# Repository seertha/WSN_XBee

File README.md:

# WSN_XBee
Red de sensores inalámbricos utilizando módulos de comunicación XBee.

Proyecto en desarrollo.

Pruebas en RPi2.

Se utiliza la placa adaptadora para GPIO v1_3

Se utiliza un menú inicial de control para seleccionar el programa principal

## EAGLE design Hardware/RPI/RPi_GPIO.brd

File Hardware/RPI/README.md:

Archivos Eagle para la placa adaptadora GPIO

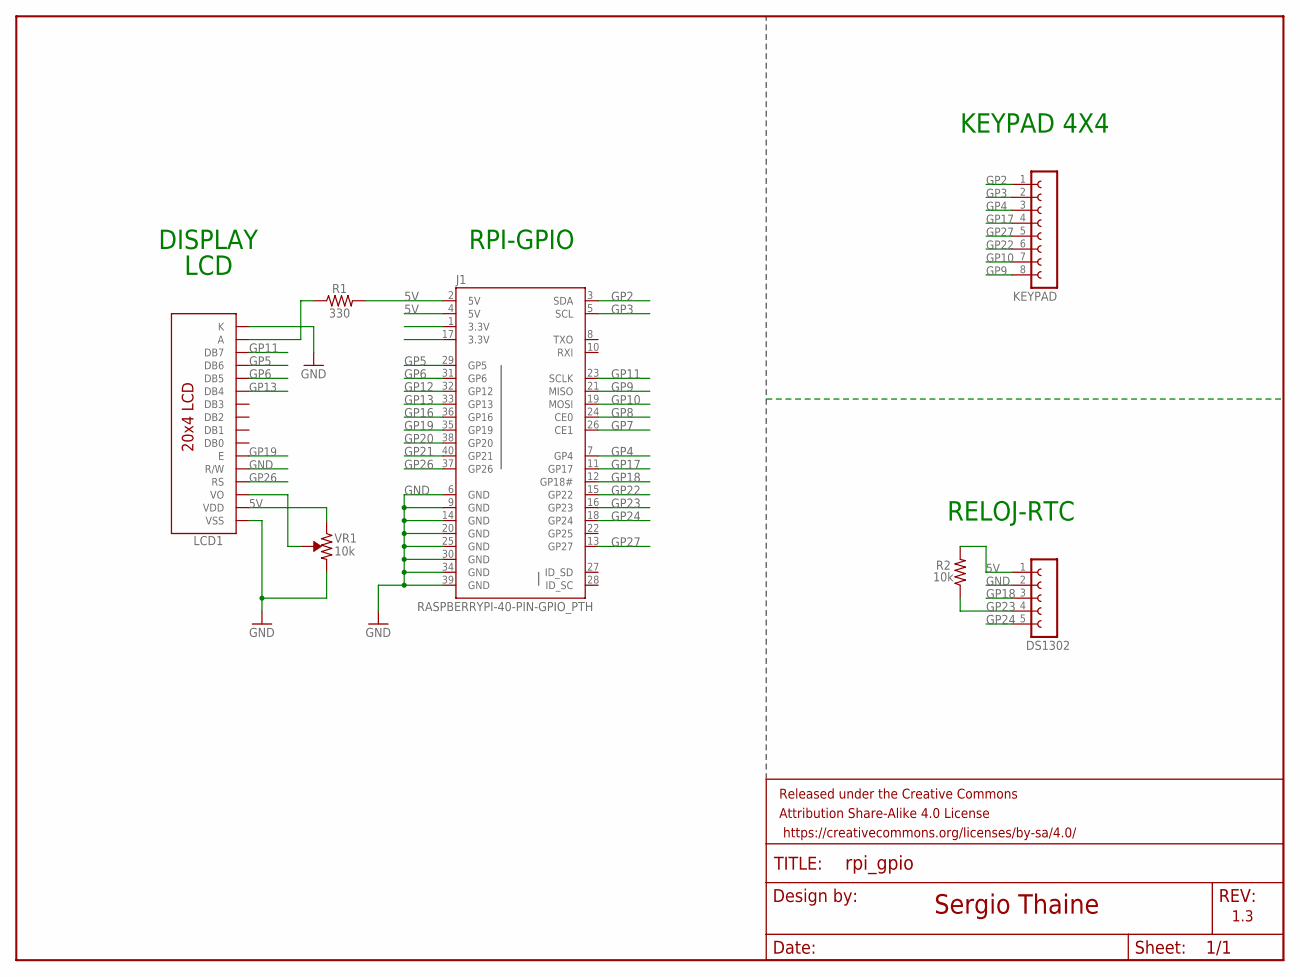
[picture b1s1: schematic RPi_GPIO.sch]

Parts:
DS1302: FE05-1
FRAME1: FRAME-LETTERNO_PACKAGE; DUMMY
J1: RASPBERRYPI-40-PIN-GPIO_PTH; 2X20_SHROUDED
KEYPAD: FE08-1; FE08
LCD1: LCD-16X2NOHOLES; LCD-16X2_NOHOLESNOSILK
R1: 330; AXIAL-0.3
R2: 10k; AXIAL-0.3
VR1: 10k; TRIMPOT-PTH-3386U

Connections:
5V: DS1302.1, J1.2 (5V), J1.4 (5V), LCD1.2 (VDD), R1.P$2 (2), R2.P$2 (2), VR1.3 (CW)
GND: DS1302.2, J1.6 (GND), J1.9 (GND), J1.14 (GND), J1.20 (GND), J1.25 (GND), J1.30 (GND), J1.34 (GND), J1.39 (GND), LCD1.1 (VSS), LCD1.5 (R/W), LCD1.16 (K), VR1.1 (CCW)
GP2: J1.3 (SDA), KEYPAD.1
GP3: J1.5 (SCL), KEYPAD.2
GP4: J1.7 (GP4), KEYPAD.3
GP5: J1.29 (GP5), LCD1.13 (DB6)
GP6: J1.31 (GP6), LCD1.12 (DB5)
GP7: J1.26 (CE1)
GP8: J1.24 (CE0)
GP9: J1.21 (MISO), KEYPAD.8
GP10: J1.19 (MOSI), KEYPAD.7
GP11: J1.23 (SCLK), LCD1.14 (DB7)
GP12: J1.32 (GP12)
GP13: J1.33 (GP13), LCD1.11 (DB4)
GP16: J1.36 (GP16)
GP17: J1.11 (GP17), KEYPAD.4
GP18: DS1302.3, J1.12 (GP18#)
GP19: J1.35 (GP19), LCD1.6 (E)
GP20: J1.38 (GP20)
GP21: J1.40 (GP21)
GP22: J1.15 (GP22), KEYPAD.6
GP23: DS1302.4, J1.16 (GP23), R2.P$1 (1)
GP24: DS1302.5, J1.18 (GP24)
GP26: J1.37 (GP26), LCD1.4 (RS)
GP27: J1.13 (GP27), KEYPAD.5
unnamed: LCD1.3 (VO), VR1.2 (WIPER)
unnamed: LCD1.15 (A), R1.P$1 (1)

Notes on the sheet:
1.3
Sergio Thaine
KEYPAD 4X4
RELOJ-RTC
RPI-GPIO
LCD
DISPLAY

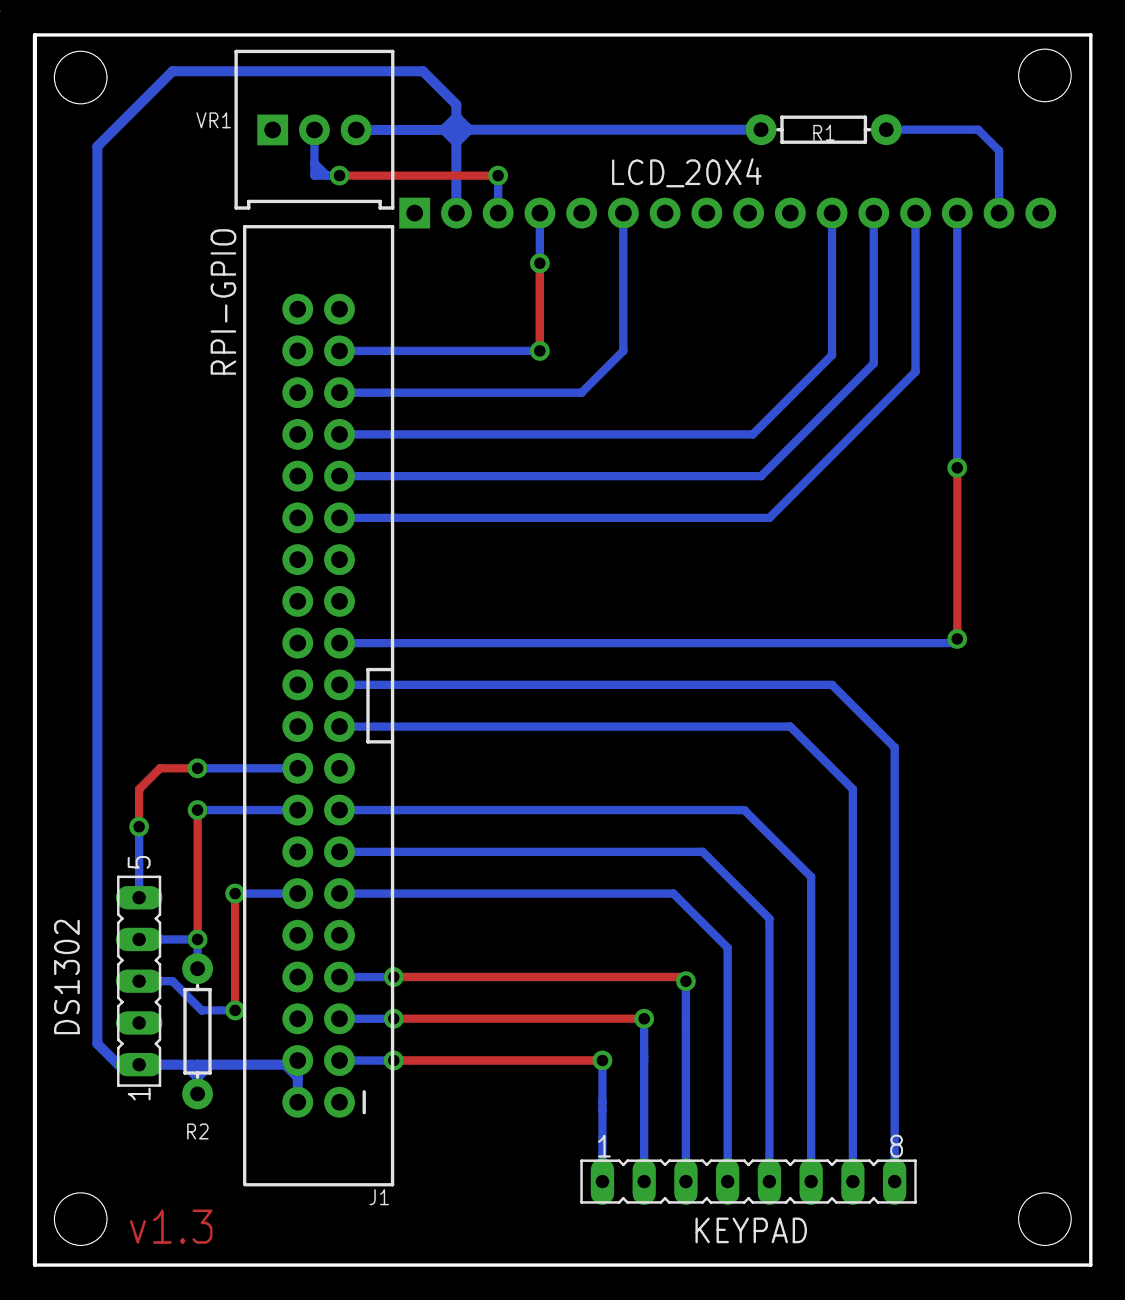
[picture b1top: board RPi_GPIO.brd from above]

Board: 2 copper layers, 64.2 x 74.9 mm, 8 parts (0 on the bottom side), 21 nets.

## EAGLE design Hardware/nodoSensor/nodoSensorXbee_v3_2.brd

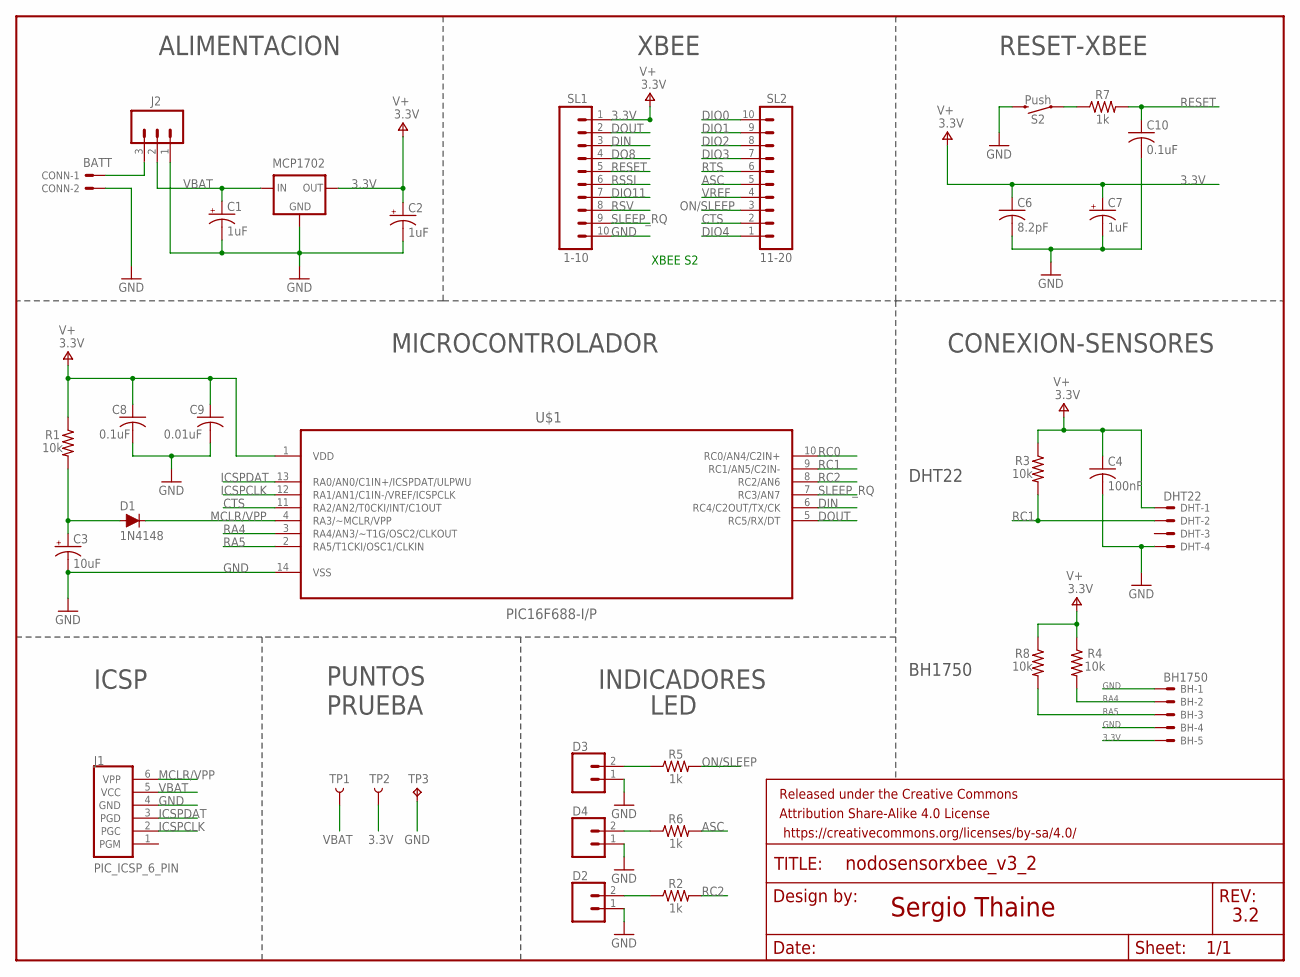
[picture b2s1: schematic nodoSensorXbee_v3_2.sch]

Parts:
BH: BH1750; 6410-05
C1, C2, C7: 1uF; E2-5
C3: 10uF; E2-5
C4: 100nF; C025-030X050
C6: 8.2pF; C025-030X050
C8, C10: 0.1uF; C025-030X050
C9: 0.01uF; C025-030X050
CONN: BATT; 6410-02
D1: 1N4148; DIODE-1N4148
D2, D3, D4: CONN_02POLAR; MOLEX-1X2
DHT: DHT22; 6410-04
FRAME1: FRAME-LETTERNO_PACKAGE; DUMMY
J1: PIC_ICSP_6_PIN; MOLEX-1X6
J2: CONN_03POLAR; MOLEX-1X3
MCP1702: 3.3v; TO92
R1, R3, R4, R8: 10k; AXIAL-0.3-KIT
R2, R5, R6, R7: 1k; AXIAL-0.3-KIT
S2: Push; TACTILE_SWITCH_PTH_6.0MM
SL1: 1-10; 10P
SL2: 11-20; 10P
TP1: VBAT; PAD.03X.05
TP2: 3.3V; PAD.03X.05
TP3: TPPAD1-13; P1-13
U$1: PIC16F688-I/P; DIP254P762X533-14

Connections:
3.3V: BH.5, C2.+, C4.1, C6.1, C7.+, C8.1, C9.1, DHT.1, MCP1702.3 (OUT), R1.P$1 (1), R3.P$1 (1), R4.P$1 (1), R8.P$1 (1), SL1.1, TP2.P$1, U$1.1 (VDD)
ASC: R6.P$2 (2), SL2.5
CTS: SL2.2, U$1.11 (RA2/AN2/T0CKI/INT/C1OUT)
DIN: SL1.3, U$1.6 (RC4/C2OUT/TX/CK)
DIO0: SL2.10
DIO1: SL2.9
DIO2: SL2.8
DIO3: SL2.7
DIO4: SL2.1
DIO11: SL1.7
DO8: SL1.4
DOUT: SL1.2, U$1.5 (RC5/RX/DT)
GND: BH.1, BH.4, C1.-, C2.-, C3.-, C4.2, C6.2, C7.-, C8.2, C9.2, C10.2, CONN.2, D2.1, D3.1, D4.1, DHT.4, J1.4 (GND), J2.1, MCP1702.1 (GND), S2.3 (2), SL1.10, TP3.TP, U$1.14 (VSS)
ICSPCLK: J1.2 (PGC), U$1.12 (RA1/AN1/C1IN-/VREF/ICSPCLK)
ICSPDAT: J1.3 (PGD), U$1.13 (RA0/AN0/C1IN+/ICSPDAT/ULPWU)
MCLR/VPP: D1.C, J1.6 (VPP), U$1.4 (RA3/~MCLR/VPP)
unnamed: CONN.1, J2.3
unnamed: C3.+, D1.A, R1.P$2 (2)
unnamed: D3.2, R5.P$1 (1)
unnamed: D4.2, R6.P$1 (1)
unnamed: D2.2, R2.P$1 (1)
unnamed: R7.P$1 (1), S2.1
ON/SLEEP: R5.P$2 (2), SL2.3
RA4: BH.2, R4.P$2 (2), U$1.3 (RA4/AN3/~T1G/OSC2/CLKOUT)
RA5: BH.3, R8.P$2 (2), U$1.2 (RA5/T1CKI/OSC1/CLKIN)
RC0: U$1.10 (RC0/AN4/C2IN+)
RC1: DHT.2, R3.P$2 (2), U$1.9 (RC1/AN5/C2IN-)
RC2: R2.P$2 (2), U$1.8 (RC2/AN6)
RESET: C10.1, R7.P$2 (2), SL1.5
RSSI: SL1.6
RSV: SL1.8
RTS: SL2.6
SLEEP_RQ: SL1.9, U$1.7 (RC3/AN7)
VBAT: C1.+, J1.5 (VCC), J2.2, MCP1702.2 (IN), TP1.P$1
VREF: SL2.4

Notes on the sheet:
XBEE S2
Sergio Thaine
3.2
3.3V
ALIMENTACION
XBEE
RESET-XBEE
CONEXION-SENSORES
MICROCONTROLADOR
DHT22
BH1750
ICSP
PUNTOS PRUEBA
LED
INDICADORES

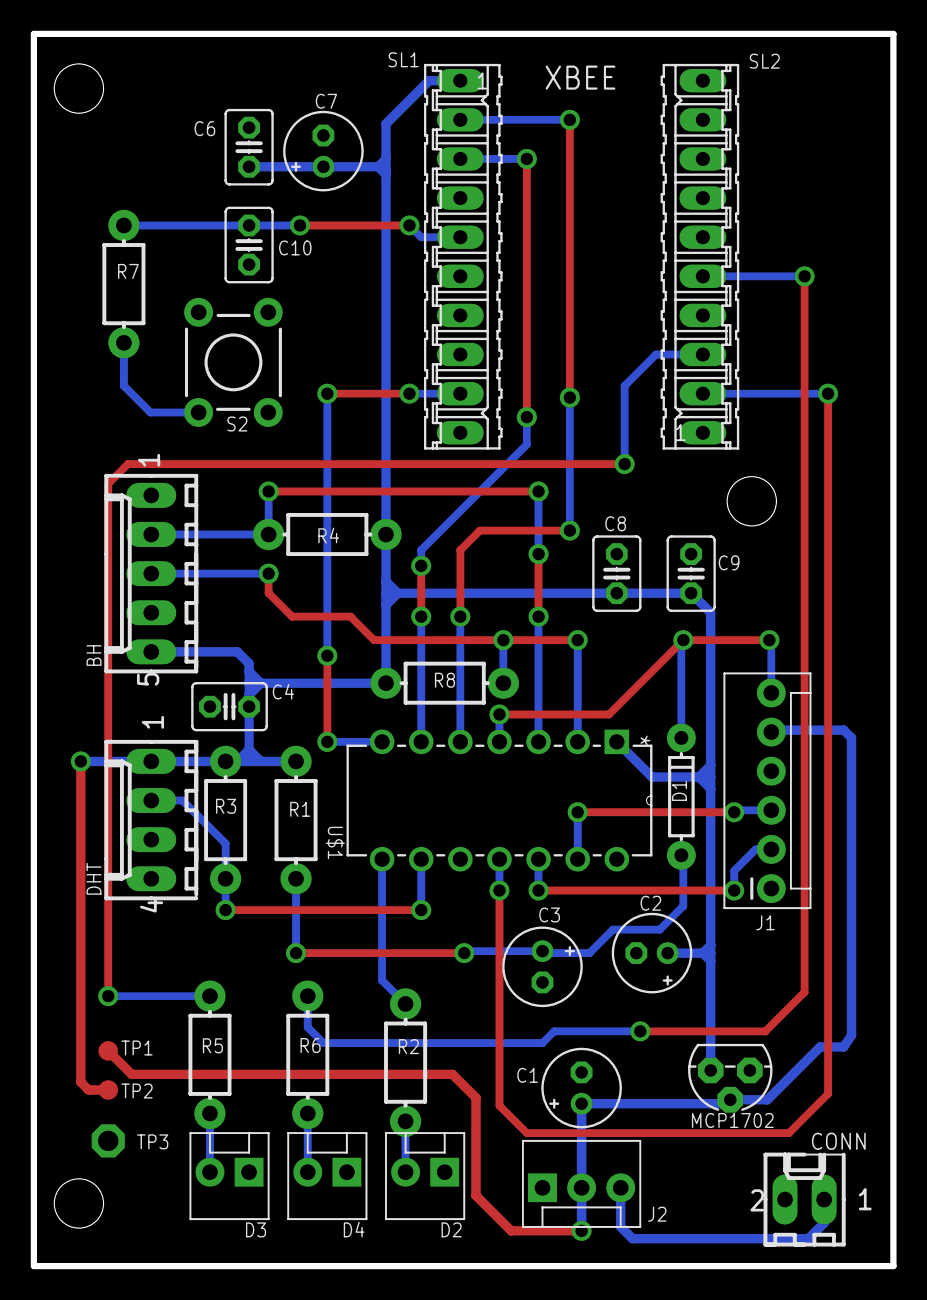
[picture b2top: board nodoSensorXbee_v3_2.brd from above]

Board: 2 copper layers, 55.8 x 80.0 mm, 35 parts (0 on the bottom side), 23 nets.

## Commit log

2017-06-18 Inicio de repositorio
2017-06-18 correciones menores
2017-06-19 xbee nodo creado y probado
2017-06-20 IndexError y Unicode Error
2017-06-21 correccion errores
2017-07-09 serial port close
2017-07-10 inicio basedatos
2017-07-14 prueba de funcionamiento general
2017-07-18 prueba base automatica
2017-07-18 borrado de comentarios
2017-07-18 Update README.md
    Inicio del repositorio
2017-07-18 Update modulosXbee.py
    Corrección en la dirección de la base de datos
2017-07-19 cambios readme
2017-07-19 cambios direccion db
2017-07-19 Update README.md
    actualizacion Readme
2017-07-19 Update README.md
    cambios readme
2017-07-19 prueba vscode
2017-07-19 prueba lcd
2017-07-19 Delete lcd_test01
    archivos innecesarios
2017-07-19 corrección lcd init
2017-07-20 cambios para pruebas con LCD
2017-08-07 cambios en lcd_db_test
2017-08-08 progrma de prueba para menu con pulsador
2017-08-08 correción de errores
2017-08-09 solucion de problemas
2017-08-09 en funcionamiento basico
2017-08-09 menu nodos sensor prueba
2017-08-10 bases de datos para pruebas
2017-08-11 configuracion de datos para pruebas
2017-08-12 correccion de errores
2017-08-12 añadiendo datos
2017-09-20 modificaciones en la visualizacion
2017-09-21 modificación para lcd 20x4
2017-09-22 corrección de errores
2017-09-22 módulo para el manejo de la base de datos incluido
2017-09-22 módulo para el manejo de la base de datos
2017-10-16 archivos para la visualizacion en el displat lcd
2018-01-05 Update README.md
    Nueva rama creada para realizar pruebas con la placa adaptadora para GPIO v1_3
2018-03-20 Corrección en los pines de control para el teclado y la pantalla lcd
2018-03-20 Inclusión de módulo db
2018-03-20 py cache display y teclado
2018-03-21 corrección formato fecha_hora
2018-03-27 cambio en el orden de ficheros
2018-03-28 Menu inicial agragado (parcial)
2018-03-28 Update README.md
    Se añade el menú de control inicial
2018-03-28 Ampliación de menu inicio
2018-03-29 Registro de teclado
2018-03-29 Prueba de inicio
2018-03-29 archivo pendiente
2018-03-29 sin cambios
2018-03-29 versiones de prueba
2018-03-29 pruebas con módulo pantallaLCD
2018-03-31 información de red añadida a la pantalla infoGen
2018-04-02 pantalla opciones añadida a selección de modo
2018-04-02 métodos reiniciar/apagar incluidos
2018-04-03 correcciones en pantalla opciones
2018-04-04 corrección info general nodos en red
2018-04-04 pycache update
2018-04-05 pantalla RESUMEN-PROMEDIO corregida
2018-04-05 maxMin día corregido
2018-04-16 Update README.md
    Branch logging
2018-04-16 eliminación de archivos innecesarios o duplicados
2018-04-17 pruebas con registros logs
2018-04-17 carpeta logs creada
2018-04-17 Corrección de errores y pruebas de logs
2018-04-18 Código alternativo en comentarios quitado
2018-04-21 registro de logs al conectarse los nodos sensores
2020-02-07 Set theme jekyll-theme-minimal
2020-02-07 gitignore añadido
2020-02-07 vscode gitignore
2020-02-07 archivo borrado
2020-02-07 .vscode borrado
2020-02-07 Create index.html
    página index.html
2020-02-07 prueba index
2020-02-18 Archivos para github pages
2020-02-18 Create README.md
    Carpeta Hardware creada
2020-02-18 Create README.md
    Carpeta Software creada
2020-02-18 Create README.md
    Carpeta PIC16F688 creada
2020-02-18 Create README.md
    Carpeta RPI creada
2020-02-18 Create README.md
    Carpeta XBEE creada
2020-02-18 Update README.md
    Xbee añadido
2020-02-18 Rename visualizacion_lcd2.py to Software/RPI/visualizacion_lcd2.py
    Cambio de ubicación a Software/RPI/
2020-02-18 Rename teclado_4x4.py to Software/RPI/teclado_4x4.py
    Cambio de ubicación a Software/RPI/
2020-02-18 Rename principal.py to Software/RPI/principal.py
    Cambio de ubicación a Software/RPI/
2020-02-18 Rename pantallas2.py to Software/RPI/pantallas2.py
    Cambio de ubicación a Software/RPI/
2020-02-18 Rename pantallaLCD.py to Software/RPI/pantallaLCD.py
    Cambio de ubicación a Software/RPI/
2020-02-18 Rename modulosXbee.py to Software/RPI/modulosXbee.py
    Cambio de ubicación a Software/RPI/
2020-02-18 Rename base_datos.py to Software/RPI/base_datos.py
    Cambio de ubicación a Software/RPI/
2020-02-18 Cambio de ubicación a Software/RPI/
2020-02-18 Archivo corregido
2020-02-18 Create README.md
    Archivos Eagle para el nodo sensor
2020-02-18 sch y brd agregados
2020-02-18 Archivos sch y brd agregados
2020-02-18 Archivos para PIC16F688
2020-02-18 Add files via upload
    versión en pdf del esquemático
2020-02-18 Delete nodoSensorXbee_v3_2.pdf
    Ubicación errónea de archivo
2020-02-18 Add files via upload
    Esquemático en pdf
2020-02-18 Add files via upload
    Versión pdf de la placa PCB
2020-02-18 Add files via upload
    Archivos pdf
2020-02-18 Delete nodoSensorXbee_v3_2_pcb.pdf
    Corrección de archivo
2020-02-18 Add files via upload
    Archivo pdf
2020-04-03 Requisitos de módulos
2020-05-30 index.html actualizado
2020-05-30 Imágenes actualizadas
2020-05-30 Estilo css añadido
2020-05-30 Corrección de enlaces

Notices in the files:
parts and their libraries:
SparkFun-Connectors: Licensing: Creative Commons ShareAlike 4.0 International - https://creativecommons.org/licenses/by-sa/4.0
SparkFun-Aesthetics: Released under the Creative Commons Attribution Share-Alike 4.0 License
SparkFun-Aesthetics: https://creativecommons.org/licenses/by-sa/4.0
